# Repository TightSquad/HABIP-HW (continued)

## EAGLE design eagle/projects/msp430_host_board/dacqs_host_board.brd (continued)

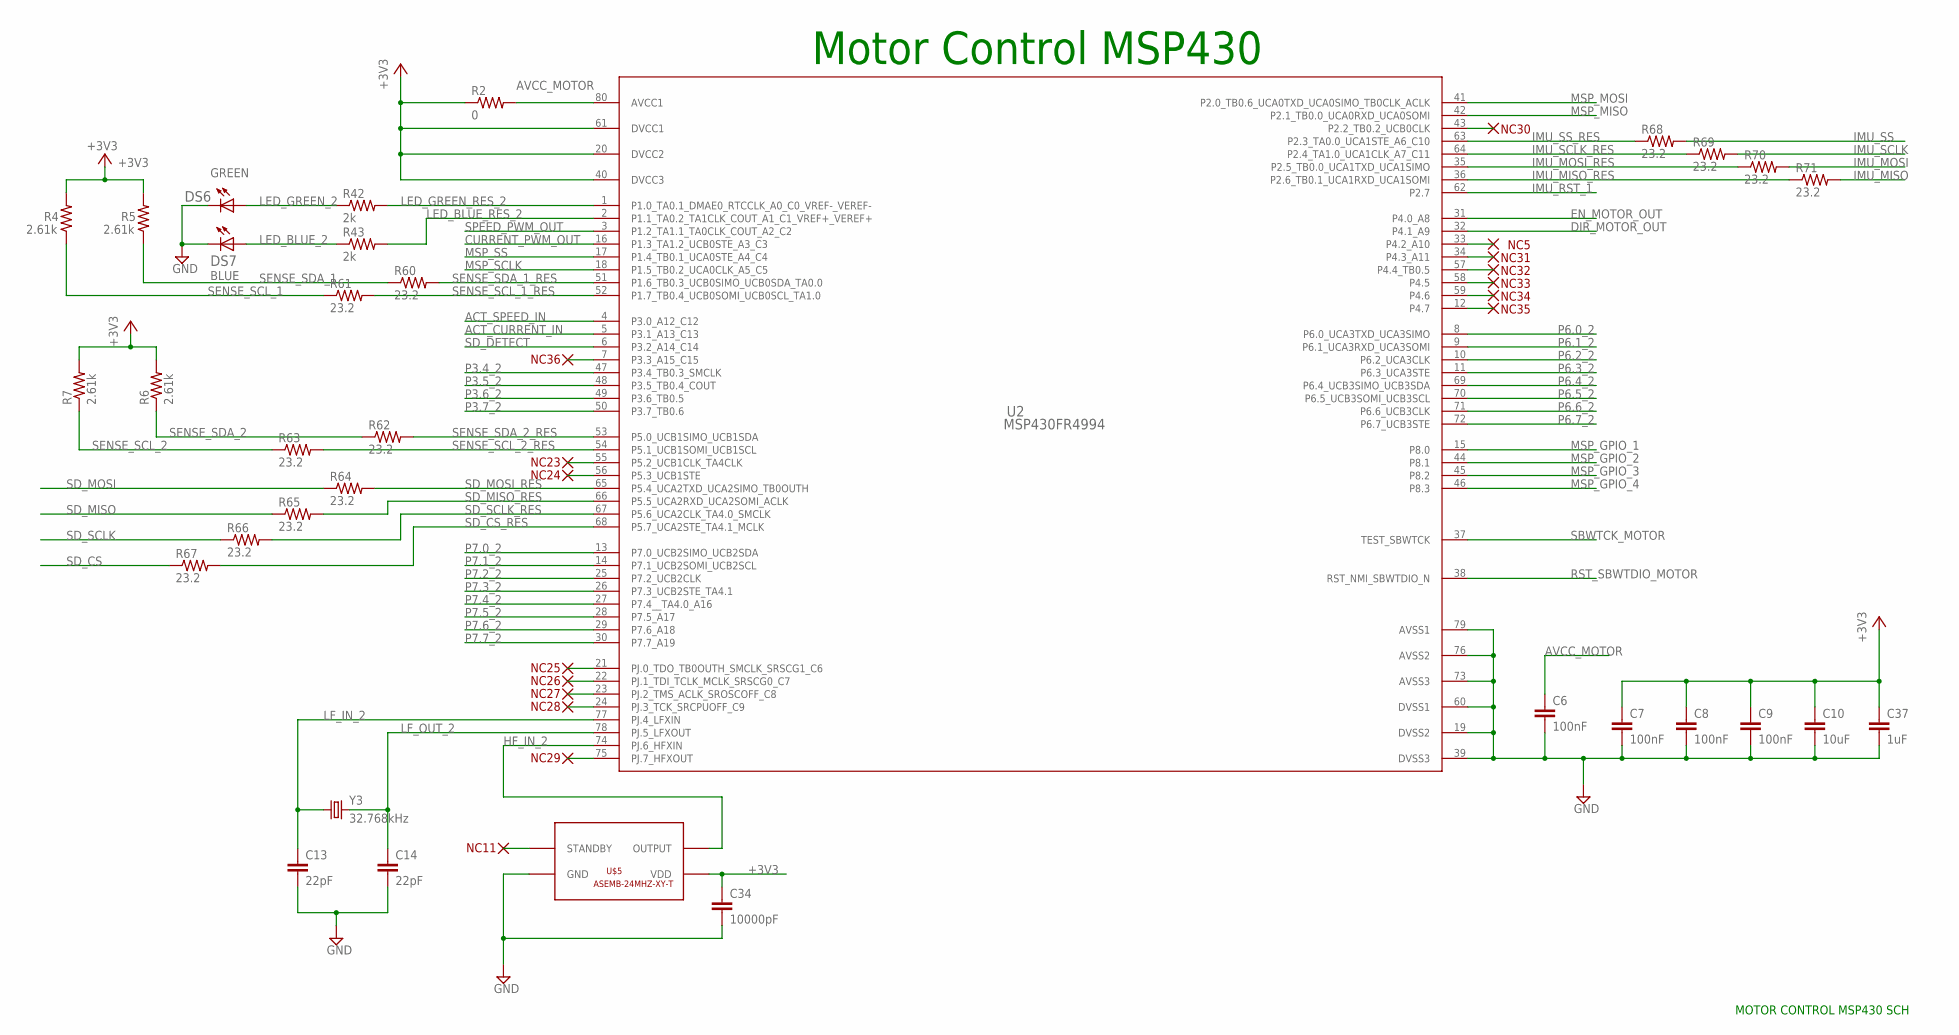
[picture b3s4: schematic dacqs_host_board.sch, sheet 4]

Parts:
C6, C7, C8, C9: 100nF; C0603
C10: 10uF; C0603
C13, C14: 22pF; C0603
C34: 10000pF; C0603
C37: 1uF; C0603
DS6: GREEN; LED0603
DS7: BLUE; LED0603
R2: 0; R0603
R4, R5, R6, R7: 2.61k; R0603
R42, R43: 2k; R0603
R60, R61, R62, R63, R64, R65, R66, R67, R68, R69, R70, R71: 23.2; R0603
U2: MSP430FR4994; PN0080A_N
U$5: ASEMB-24MHZ-XY-T; ASEMB-24MHZ-XY-T-PAC
Y3: 32.768kHz; CRYSTAL-SMD-3.2X1.5MM

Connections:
+3V3: C7.1, C8.1, C9.1, C10.1, C34.1, C37.1, R2.1, R4.2, R5.2, R6.2, R7.2, U2.20 (DVCC2), U2.40 (DVCC3), U2.61 (DVCC1), U$5.P$4 (VDD); also elsewhere on the board
ACT_CURRENT_IN: U2.5 (P3.1_A13_C13); also elsewhere on the board
ACT_SPEED_IN: U2.4 (P3.0_A12_C12); also elsewhere on the board
AVCC_MOTOR: C6.1, R2.2, U2.80 (AVCC1)
CURRENT_PWM_OUT: U2.16 (P1.3_TA1.2_UCB0STE_A3_C3); also elsewhere on the board
DIR_MOTOR_OUT: U2.32 (P4.1_A9); also elsewhere on the board
EN_MOTOR_OUT: U2.31 (P4.0_A8); also elsewhere on the board
GND: C6.2, C7.2, C8.2, C9.2, C10.2, C13.2, C14.2, C34.2, C37.2, DS6.1 (C), DS7.1 (C), U2.19 (DVSS2), U2.39 (DVSS3), U2.60 (DVSS1), U2.73 (AVSS3), U2.76 (AVSS2), U2.79 (AVSS1), U$5.P$2 (GND); also elsewhere on the board
HF_IN_2: U2.74 (PJ.6_HFXIN), U$5.P$3 (OUTPUT)
IMU_MISO: R71.2; also elsewhere on the board
IMU_MISO_RES: R71.1, U2.36 (P2.6_TB0.1_UCA1RXD_UCA1SOMI)
IMU_MOSI: R70.2; also elsewhere on the board
IMU_MOSI_RES: R70.1, U2.35 (P2.5_TB0.0_UCA1TXD_UCA1SIMO)
IMU_RST_1: U2.62 (P2.7); also elsewhere on the board
IMU_SCLK: R69.2; also elsewhere on the board
IMU_SCLK_RES: R69.1, U2.64 (P2.4_TA1.0_UCA1CLK_A7_C11)
IMU_SS: R68.2; also elsewhere on the board
IMU_SS_RES: R68.1, U2.63 (P2.3_TA0.0_UCA1STE_A6_C10)
LED_BLUE_2: DS7.2 (A), R43.1
LED_BLUE_RES_2: R43.2, U2.2 (P1.1_TA0.2_TA1CLK_COUT_A1_C1_VREF+_VERE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)
LED_GREEN_2: DS6.2 (A), R42.1
LED_GREEN_RES_2: R42.2, U2.1 (P1.0_TA0.1_DMAE0_RTCCLK_A0_C0_VREF-_VER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)
LF_IN_2: C13.1, U2.77 (PJ.4_LFXIN), Y3.P$1 (1)
LF_OUT_2: C14.1, U2.78 (PJ.5_LFXOUT), Y3.P$2 (2)
MSP_GPIO_1: U2.15 (P8.0); also elsewhere on the board
MSP_GPIO_2: U2.44 (P8.1); also elsewhere on the board
MSP_GPIO_3: U2.45 (P8.2); also elsewhere on the board
MSP_GPIO_4: U2.46 (P8.3); also elsewhere on the board
MSP_MISO: U2.42 (P2.1_TB0.0_UCA0RXD_UCA0SOMI); also elsewhere on the board
MSP_MOSI: U2.41 (P2.0_TB0.6_UCA0TXD_UCA0SIMO_TB0CLK_ACLK); also elsewhere on the board
MSP_SCLK: U2.18 (P1.5_TB0.2_UCA0CLK_A5_C5); also elsewhere on the board
MSP_SS: U2.17 (P1.4_TB0.1_UCA0STE_A4_C4); also elsewhere on the board
P3.4_2: U2.47 (P3.4_TB0.3_SMCLK); also elsewhere on the board
P3.5_2: U2.48 (P3.5_TB0.4_COUT); also elsewhere on the board
P3.6_2: U2.49 (P3.6_TB0.5); also elsewhere on the board
P3.7_2: U2.50 (P3.7_TB0.6); also elsewhere on the board
P6.0_2: U2.8 (P6.0_UCA3TXD_UCA3SIMO); also elsewhere on the board
P6.1_2: U2.9 (P6.1_UCA3RXD_UCA3SOMI); also elsewhere on the board
P6.2_2: U2.10 (P6.2_UCA3CLK); also elsewhere on the board
P6.3_2: U2.11 (P6.3_UCA3STE); also elsewhere on the board
P6.4_2: U2.69 (P6.4_UCB3SIMO_UCB3SDA)
P6.5_2: U2.70 (P6.5_UCB3SOMI_UCB3SCL); also elsewhere on the board
P6.6_2: U2.71 (P6.6_UCB3CLK); also elsewhere on the board
P6.7_2: U2.72 (P6.7_UCB3STE); also elsewhere on the board
P7.0_2: U2.13 (P7.0_UCB2SIMO_UCB2SDA); also elsewhere on the board
P7.1_2: U2.14 (P7.1_UCB2SOMI_UCB2SCL); also elsewhere on the board
P7.2_2: U2.25 (P7.2_UCB2CLK); also elsewhere on the board
P7.3_2: U2.26 (P7.3_UCB2STE_TA4.1); also elsewhere on the board
P7.4_2: U2.27 (P7.4__TA4.0_A16); also elsewhere on the board
P7.5_2: U2.28 (P7.5_A17); also elsewhere on the board
P7.6_2: U2.29 (P7.6_A18); also elsewhere on the board
P7.7_2: U2.30 (P7.7_A19); also elsewhere on the board
RST_SBWTDIO_MOTOR: U2.38 (RST_NMI_SBWTDIO_N); also elsewhere on the board
SBWTCK_MOTOR: U2.37 (TEST_SBWTCK); also elsewhere on the board
SD_CS: R67.1; also elsewhere on the board
SD_CS_RES: R67.2, U2.68 (P5.7_UCA2STE_TA4.1_MCLK)
SD_DETECT: U2.6 (P3.2_A14_C14); also elsewhere on the board
SD_MISO: R65.1; also elsewhere on the board
SD_MISO_RES: R65.2, U2.66 (P5.5_UCA2RXD_UCA2SOMI_ACLK)
SD_MOSI: R64.1; also elsewhere on the board
SD_MOSI_RES: R64.2, U2.65 (P5.4_UCA2TXD_UCA2SIMO_TB0OUTH)
SD_SCLK: R66.1; also elsewhere on the board
SD_SCLK_RES: R66.2, U2.67 (P5.6_UCA2CLK_TA4.0_SMCLK)
SENSE_SCL_1: R4.1, R61.1; also elsewhere on the board
SENSE_SCL_1_RES: R61.2, U2.52 (P1.7_TB0.4_UCB0SOMI_UCB0SCL_TA1.0)
SENSE_SCL_2: R7.1, R63.1; also elsewhere on the board
SENSE_SCL_2_RES: R63.2, U2.54 (P5.1_UCB1SOMI_UCB1SCL)
SENSE_SDA_1: R5.1, R60.1; also elsewhere on the board
SENSE_SDA_1_RES: R60.2, U2.51 (P1.6_TB0.3_UCB0SIMO_UCB0SDA_TA0.0)
SENSE_SDA_2: R6.1, R62.1; also elsewhere on the board
SENSE_SDA_2_RES: R62.2, U2.53 (P5.0_UCB1SIMO_UCB1SDA)
SPEED_PWM_OUT: U2.3 (P1.2_TA1.1_TA0CLK_COUT_A2_C2); also elsewhere on the board

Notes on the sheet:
Motor Control MSP430
MOTOR CONTROL MSP430 SCH

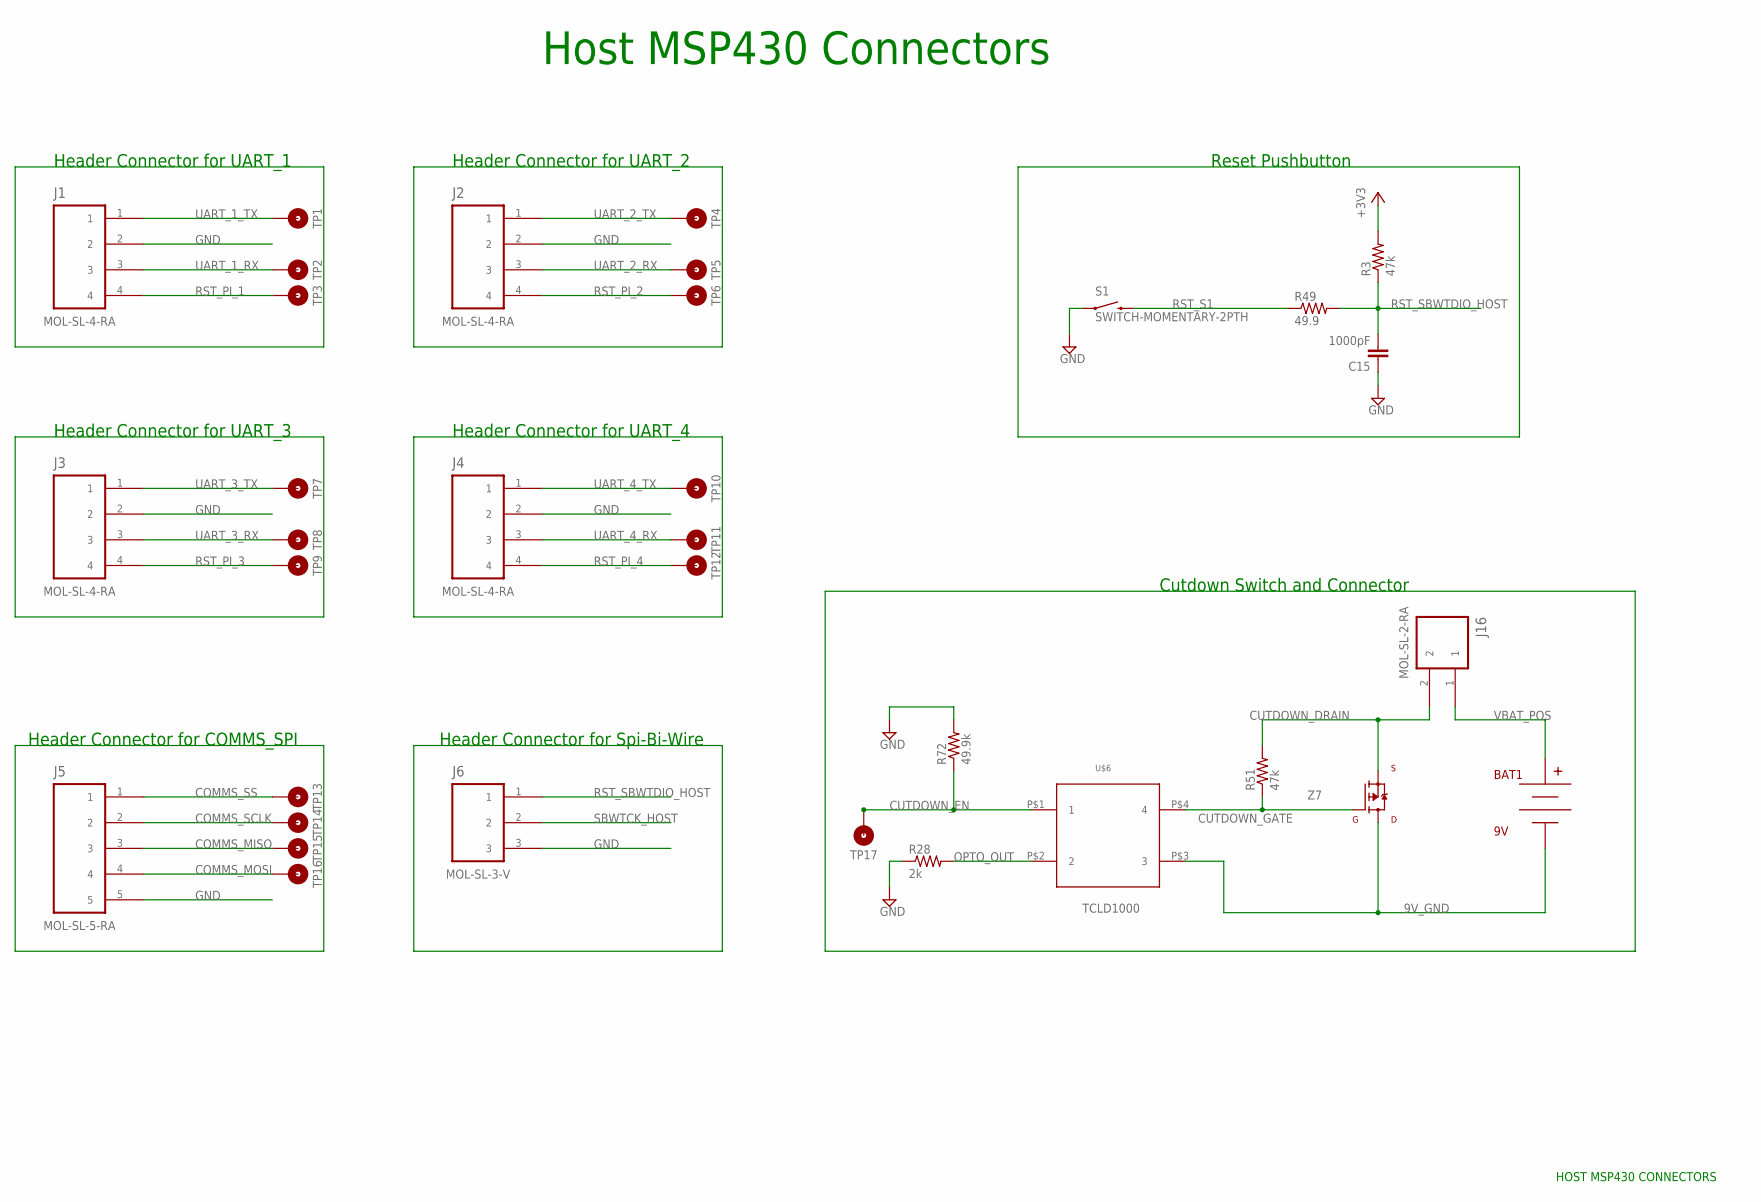
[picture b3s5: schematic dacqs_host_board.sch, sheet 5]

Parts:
BAT1: 9V; BC9VPC
C15: 1000pF; C0603
J1, J2, J3, J4: MOL-SL-4-RA; MOLSL-4-RA
J5: MOL-SL-5-RA; MOLSL-5-RA
J6: MOL-SL-3-V; MOLSL-3-V
J16: MOL-SL-2-RA; MOLSL-2-RA
R3, R51: 47k; R0603
R28: 2k; R0603
R49: 49.9; R0603
R72: 49.9k; R0603
S1: SWITCH-MOMENTARY-2PTH; TACTILE-PTH
TP1, TP2, TP3, TP4, TP5, TP6, TP7, TP8, TP9, TP10, TP11, TP12, TP13, TP14, TP15, TP16, TP17: TEST_POINT_TP10R_SMD_10R_SMD; TP10R
U$6: TCLD1000
Z7: NTD2955T4G

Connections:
9V_GND: BAT1.V-, U$6.P$3 (3), Z7.P$3 (D)
+3V3: R3.2; also elsewhere on the board
COMMS_MISO: J5.3, TP15.TP; also elsewhere on the board
COMMS_MOSI: J5.4, TP16.TP; also elsewhere on the board
COMMS_SCLK: J5.2, TP14.TP; also elsewhere on the board
COMMS_SS: J5.1, TP13.TP; also elsewhere on the board
CUTDOWN_DRAIN: J16.2, R51.2, Z7.P$2 (S)
CUTDOWN_EN: R72.1, TP17.TP, U$6.P$1 (1); also elsewhere on the board
CUTDOWN_GATE: R51.1, U$6.P$4 (4), Z7.P$1 (G)
GND: C15.1, J1.2, J2.2, J3.2, J4.2, J5.5, J6.3, R28.1, R72.2, S1.1; also elsewhere on the board
OPTO_OUT: R28.2, U$6.P$2 (2)
RST_PI_1: J1.4, TP3.TP; also elsewhere on the board
RST_PI_2: J2.4, TP6.TP; also elsewhere on the board
RST_PI_3: J3.4, TP9.TP; also elsewhere on the board
RST_PI_4: J4.4, TP12.TP; also elsewhere on the board
RST_S1: R49.1, S1.3 (2)
RST_SBWTDIO_HOST: C15.2, J6.1, R3.1, R49.2; also elsewhere on the board
SBWTCK_HOST: J6.2; also elsewhere on the board
UART_1_RX: J1.3, TP2.TP; also elsewhere on the board
UART_1_TX: J1.1, TP1.TP; also elsewhere on the board
UART_2_RX: J2.3, TP5.TP; also elsewhere on the board
UART_2_TX: J2.1, TP4.TP; also elsewhere on the board
UART_3_RX: J3.3, TP8.TP; also elsewhere on the board
UART_3_TX: J3.1, TP7.TP; also elsewhere on the board
UART_4_RX: J4.3, TP11.TP; also elsewhere on the board
UART_4_TX: J4.1, TP10.TP; also elsewhere on the board
VBAT_POS: BAT1.V+, J16.1

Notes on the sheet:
Header Connector for UART_1
Header Connector for UART_2
Header Connector for UART_3
Header Connector for UART_4
Header Connector for COMMS_SPI
Reset Pushbutton
Header Connector for Spi-Bi-Wire
Cutdown Switch and Connector
Host MSP430 Connectors
HOST MSP430 CONNECTORS

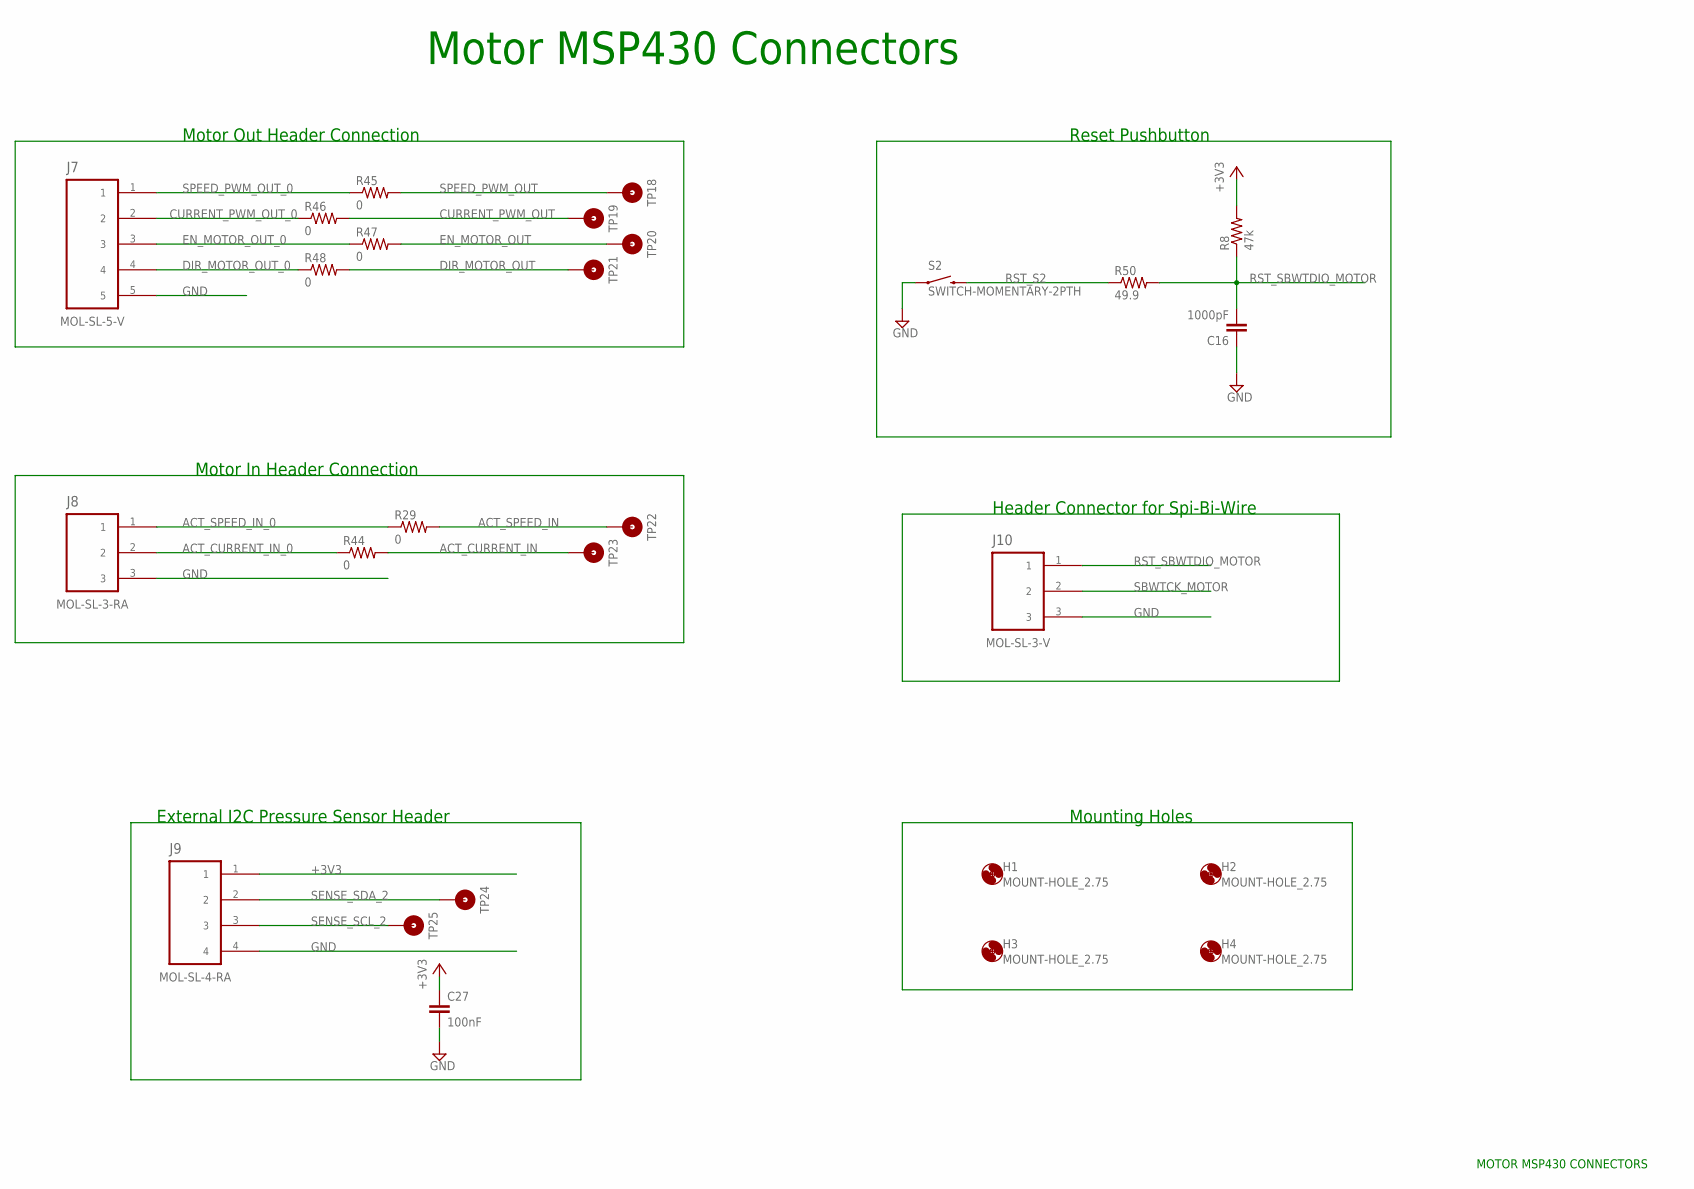
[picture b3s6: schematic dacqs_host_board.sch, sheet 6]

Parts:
C16: 1000pF; C0603
C27: 100nF; C0603
H1, H2, H3, H4: MOUNT-HOLE_2.75; 2,75_HOLE_RASPI
J7: MOL-SL-5-V; MOLSL-5-V
J8: MOL-SL-3-RA; MOLSL-3-RA
J9: MOL-SL-4-RA; MOLSL-4-RA
J10: MOL-SL-3-V; MOLSL-3-V
R8: 47k; R0603
R29, R44, R45, R46, R47, R48: 0; R0603
R50: 49.9; R0603
S2: SWITCH-MOMENTARY-2PTH; TACTILE-PTH
TP18, TP19, TP20, TP21, TP22, TP23, TP24, TP25: TEST_POINT_TP10R_SMD_10R_SMD; TP10R

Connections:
+3V3: C27.1, J9.1, R8.2; also elsewhere on the board
ACT_CURRENT_IN: R44.2, TP23.TP; also elsewhere on the board
ACT_CURRENT_IN_0: J8.2, R44.1
ACT_SPEED_IN: R29.2, TP22.TP; also elsewhere on the board
ACT_SPEED_IN_0: J8.1, R29.1
CURRENT_PWM_OUT: R46.2, TP19.TP; also elsewhere on the board
CURRENT_PWM_OUT_0: J7.2, R46.1
DIR_MOTOR_OUT: R48.2, TP21.TP; also elsewhere on the board
DIR_MOTOR_OUT_0: J7.4, R48.1
EN_MOTOR_OUT: R47.2, TP20.TP; also elsewhere on the board
EN_MOTOR_OUT_0: J7.3, R47.1
GND: C16.1, C27.2, J7.5, J8.3, J9.4, J10.3, S2.1; also elsewhere on the board
RST_S2: R50.1, S2.3 (2)
RST_SBWTDIO_MOTOR: C16.2, J10.1, R8.1, R50.2; also elsewhere on the board
SBWTCK_MOTOR: J10.2; also elsewhere on the board
SENSE_SCL_2: J9.3, TP25.TP; also elsewhere on the board
SENSE_SDA_2: J9.2, TP24.TP; also elsewhere on the board
SPEED_PWM_OUT: R45.2, TP18.TP; also elsewhere on the board
SPEED_PWM_OUT_0: J7.1, R45.1

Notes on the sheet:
Motor Out Header Connection
Motor In Header Connection
External I2C Pressure Sensor Header
Header Connector for Spi-Bi-Wire
Reset Pushbutton
Motor MSP430 Connectors
Mounting Holes
MOTOR MSP430 CONNECTORS

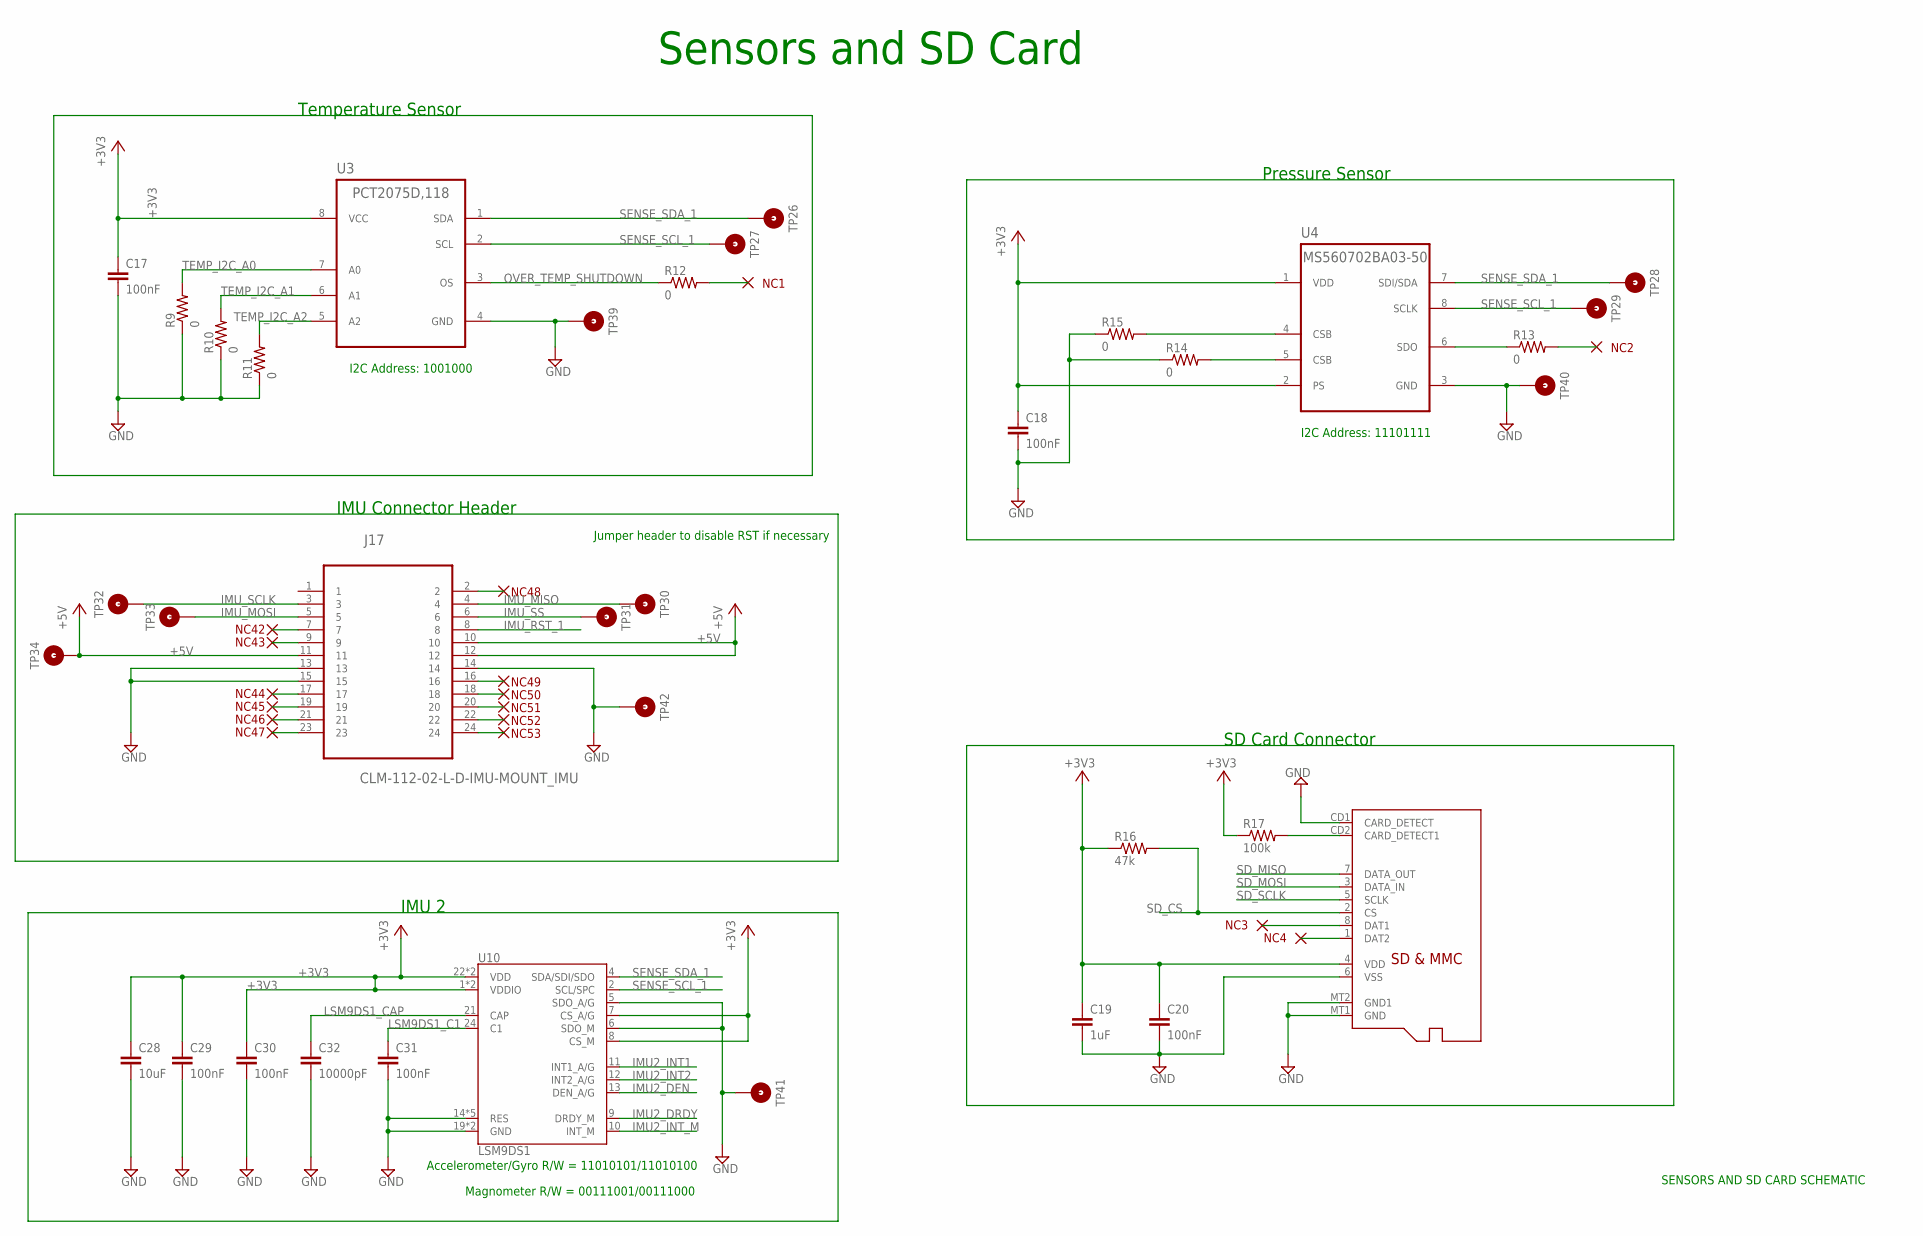
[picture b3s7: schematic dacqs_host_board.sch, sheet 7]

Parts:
C17, C18, C20, C29, C30, C31: 100nF; C0603
C19: 1uF; C0603
C28: 10uF; C0603
C32: 10000pF; C0603
J17: CLM-112-02-L-D-IMU-MOUNT_IMU; SAMTEC_CLM-112-02-L-D-IMU-MOUNT
R9, R10, R11, R12, R13, R14, R15: 0; R0603
R16: 47k; R0603
R17: 100k; R0603
TP26, TP27, TP28, TP29, TP30, TP31, TP32, TP33, TP34, TP39, TP40, TP41, TP42: TEST_POINT_TP10R_SMD_10R_SMD; TP10R
U3: PCT2075D,118; SOIC127P130X0600-8N
U4: MS560702BA03-50; SMD125P110X060-8N
U10: LSM9DS1; LGA24-8X4
U$1: MICROSD

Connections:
+3V3: C17.1, C18.1, C19.1, C20.1, C28.1, C29.1, C30.1, R16.1, R17.1, U3.8 (VCC), U4.1 (VDD), U4.2 (PS), U10.1 (VDDIO), U10.3 (VDDIO), U10.7 (CS_A/G), U10.8 (CS_M), U10.22 (VDD), U10.23 (VDD), U$1.4 (VDD); also elsewhere on the board
+5V: J17.10, J17.11, J17.12, TP34.TP; also elsewhere on the board
GND: C17.2, C18.2, C19.2, C20.2, C28.2, C29.2, C30.2, C31.2, C32.2, J17.13, J17.14, J17.15, R9.1, R10.1, R11.1, R14.1, R15.1, TP39.TP, TP40.TP, TP41.TP, TP42.TP, U3.4 (GND), U4.3 (GND), U10.5 (SDO_A/G), U10.6 (SDO_M), U10.14 (RES), U10.15 (RES), U10.16 (RES), U10.17 (RES), U10.18 (RES), U10.19 (GND), U10.20 (GND), U$1.6 (VSS), U$1.CD1 (CARD_DETECT), U$1.MT1 (GND), U$1.MT2 (GND1); also elsewhere on the board
IMU2_DEN: U10.13 (DEN_A/G); also elsewhere on the board
IMU2_DRDY: U10.9 (DRDY_M); also elsewhere on the board
IMU2_INT1: U10.11 (INT1_A/G); also elsewhere on the board
IMU2_INT2: U10.12 (INT2_A/G); also elsewhere on the board
IMU2_INT_M: U10.10 (INT_M); also elsewhere on the board
IMU_MISO: J17.4, TP30.TP; also elsewhere on the board
IMU_MOSI: J17.5, TP33.TP; also elsewhere on the board
IMU_RST_1: J17.8; also elsewhere on the board
IMU_SCLK: J17.3, TP32.TP; also elsewhere on the board
IMU_SS: J17.6, TP31.TP; also elsewhere on the board
LSM9DS1_C1: C31.1, U10.24 (C1)
LSM9DS1_CAP: C32.1, U10.21 (CAP)
unnamed: R15.2, U4.4 (CSB)
unnamed: R14.2, U4.5 (CSB)
unnamed: R13.1, U4.6 (SDO)
OVER_TEMP_SHUTDOWN: R12.1, U3.3 (OS)
SD_CS: R16.2, U$1.2 (CS); also elsewhere on the board
SD_DETECT: R17.2, U$1.CD2 (CARD_DETECT1); also elsewhere on the board
SD_MISO: U$1.7 (DATA_OUT); also elsewhere on the board
SD_MOSI: U$1.3 (DATA_IN); also elsewhere on the board
SD_SCLK: U$1.5 (SCLK); also elsewhere on the board
SENSE_SCL_1: TP27.TP, TP29.TP, U3.2 (SCL), U4.8 (SCLK), U10.2 (SCL/SPC); also elsewhere on the board
SENSE_SDA_1: TP26.TP, TP28.TP, U3.1 (SDA), U4.7 (SDI/SDA), U10.4 (SDA/SDI/SDO); also elsewhere on the board
TEMP_I2C_A0: R9.2, U3.7 (A0)
TEMP_I2C_A1: R10.2, U3.6 (A1)
TEMP_I2C_A2: R11.2, U3.5 (A2)

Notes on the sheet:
Temperature Sensor
Pressure Sensor
IMU Connector Header
Jumper header to disable RST if necessary
SD Card Connector
Sensors and SD Card
IMU 2
SENSORS AND SD CARD SCHEMATIC
I2C Address: 1001000
I2C Address: 11101111
Accelerometer/Gyro R/W = 11010101/11010100
Magnometer R/W = 00111001/00111000

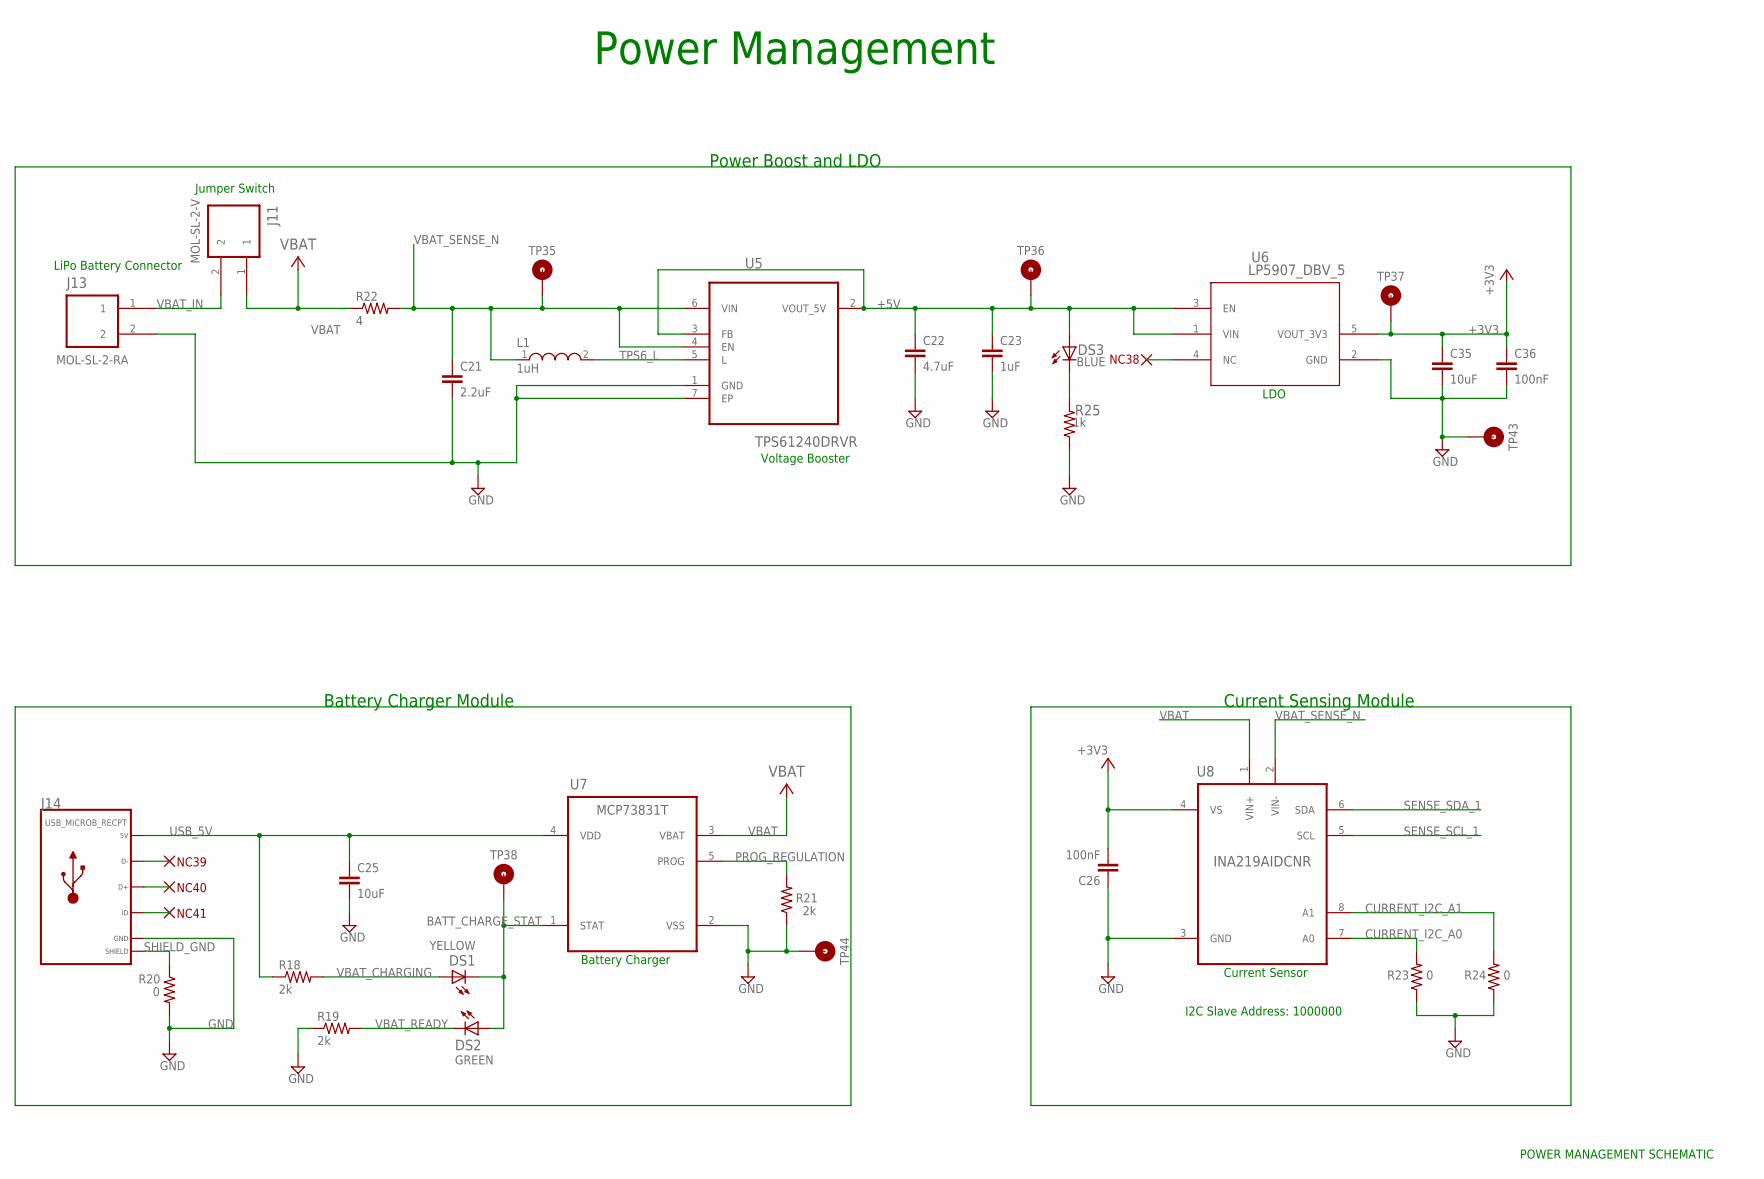
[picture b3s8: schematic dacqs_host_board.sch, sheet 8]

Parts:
C21: 2.2uF; C0603
C22: 4.7uF; C0603
C23: 1uF; C0603
C25, C35: 10uF; C0603
C26, C36: 100nF; C0603
DS1: YELLOW; LED0603
DS2: GREEN; LED0603
DS3: BLUE; LED0603
J11: MOL-SL-2-V; MOLSL-2-V
J13: MOL-SL-2-RA; MOLSL-2-RA
J14: USB_MICROB_RECPT; MICROUSB-RIGHT
L1: 1uH; WE-PMI_0805
R18, R19, R21: 2k; R0603
R20, R23, R24: 0; R0603
R22: 4; R0603
R25: 1k; R0603
TP35, TP36, TP37, TP38, TP43, TP44: TEST_POINT_TP10R_SMD_10R_SMD; TP10R
U5: TPS61240DRVR; SON65P200X200X80-7N
U6: LP5907_DBV_5; DBV5
U7: MCP73831T; SOT23P110X060-5N
U8: INA219AIDCNR; SOT65P110X045-8N

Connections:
+3V3: C26.2, C35.1, C36.1, TP37.TP, U6.5 (VOUT_3V3), U8.4 (VS); also elsewhere on the board
+5V: C22.1, C23.1, DS3.2 (A), TP36.TP, U5.2 (VOUT_5V), U5.3 (FB), U6.1 (VIN), U6.3 (EN); also elsewhere on the board
BATT_CHARGE_STAT: DS1.1 (C), DS2.2 (A), TP38.TP, U7.1 (STAT)
CURRENT_I2C_A0: R23.2, U8.7 (A0)
CURRENT_I2C_A1: R24.2, U8.8 (A1)
GND: C21.2, C22.2, C23.2, C25.2, C26.1, C35.2, C36.2, J13.2, J14.5 (GND), R19.1, R20.2, R21.1, R23.1, R24.1, R25.1, TP43.TP, TP44.TP, U5.1 (GND), U5.7 (EP), U6.2 (GND), U7.2 (VSS), U8.3 (GND); also elsewhere on the board
LED_BLUE_5V: DS3.1 (C), R25.2
PROG_REGULATION: R21.2, U7.5 (PROG)
SENSE_SCL_1: U8.5 (SCL); also elsewhere on the board
SENSE_SDA_1: U8.6 (SDA); also elsewhere on the board
SHIELD_GND: J14.S1 (SLD), J14.S2 (SLD), J14.S3 (SLD), J14.S4 (SLD), J14.S5 (SLD), J14.S6 (SLD), R20.1
TPS6_L: L1.2, U5.5 (L)
USB_5V: C25.1, J14.1 (5V), R18.1, U7.4 (VDD)
VBAT: J11.1, R22.1, U7.3 (VBAT), U8.1 (VIN+)
VBAT_CHARGING: DS1.2 (A), R18.2
VBAT_IN: J11.2, J13.1
VBAT_READY: DS2.1 (C), R19.2
VBAT_SENSE_N: C21.1, L1.1, R22.2, TP35.TP, U5.4 (EN), U5.6 (VIN), U8.2 (VIN-)

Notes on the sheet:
Power Management
LiPo Battery Connector
Jumper Switch
Voltage Booster
LDO
Battery Charger
Current Sensor
Battery Charger Module
Current Sensing Module
Power Boost and LDO
POWER MANAGEMENT SCHEMATIC
I2C Slave Address: 1000000

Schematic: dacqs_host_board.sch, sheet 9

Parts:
J12, J19: CONN HEADER 20POS .100" DBL; 2X10
J18: MOLSL-7-RA
R30, R33: 10.2k; R0603
R31: 10.7k; R0603
R32: 4.12k; R0603
R34, R39: 1.02k; R0603
R35: 68.1k; R0603
R36: 7.5k; R0603
R37: 1.37k; R0603
R38: 1.87k; R0603
R40: 4.32k; R0603
R41: 1.5k; R0603
Z1, Z2, Z3, Z4, Z5, Z6: MMSZ5225BT1G

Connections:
+3V3: J12.2; also elsewhere on the board
GND: J12.20, J18.7, J19.14, R36.2, R37.2, R38.2, R39.2, R40.2, R41.2, Z1.P$2, Z2.P$2, Z3.P$2, Z4.P$2, Z5.P$2, Z6.P$2; also elsewhere on the board
IMU2_DEN: J12.19; also elsewhere on the board
IMU2_DRDY: J12.11; also elsewhere on the board
IMU2_INT1: J12.15; also elsewhere on the board
IMU2_INT2: J12.17; also elsewhere on the board
IMU2_INT_M: J12.13; also elsewhere on the board
P1.2: J12.1; also elsewhere on the board
P1.4: J12.3; also elsewhere on the board
P1.5: J12.5; also elsewhere on the board
P3.4_2: J19.1; also elsewhere on the board
P3.5_2: J19.3; also elsewhere on the board
P3.6_2: J19.5; also elsewhere on the board
P3.7_2: J19.7; also elsewhere on the board
P6.0_2: J19.6; also elsewhere on the board
P6.1_2: J19.8; also elsewhere on the board
P6.2: J12.8; also elsewhere on the board
P6.2_2: J19.10; also elsewhere on the board
P6.3: J12.10; also elsewhere on the board
P6.3_2: J19.12; also elsewhere on the board
P6.4: J12.12; also elsewhere on the board
P6.5: J12.14; also elsewhere on the board
P6.5_2: J19.16; also elsewhere on the board
P6.6: J12.16; also elsewhere on the board
P6.6_2: J19.18; also elsewhere on the board
P6.7: J12.18; also elsewhere on the board
P6.7_2: J19.20; also elsewhere on the board
P7.0: J12.7; also elsewhere on the board
P7.0_2: J19.9; also elsewhere on the board
P7.1: J12.9; also elsewhere on the board
P7.1_2: J19.11; also elsewhere on the board
P7.2: J12.4; also elsewhere on the board
P7.2_2: J19.13; also elsewhere on the board
P7.3: J12.6; also elsewhere on the board
P7.3_2: J19.15; also elsewhere on the board
P7.4_2: J19.17; also elsewhere on the board
P7.5_2: J19.19; also elsewhere on the board
P7.6_2: J19.2; also elsewhere on the board
P7.7_2: J19.4; also elsewhere on the board
VBAT_CELL_1: J18.1, R35.1
VBAT_CELL_2: J18.2, R30.2
VBAT_CELL_3: J18.3, R31.2
VBAT_CELL_4: J18.4, R32.2
VBAT_CELL_5: J18.5, R33.2
VBAT_CELL_6: J18.6, R34.2
VBAT_MOD_CELL_1: R35.2, R36.1, Z1.P$1; also elsewhere on the board
VBAT_MOD_CELL_2: R30.1, R37.1, Z2.P$1; also elsewhere on the board
VBAT_MOD_CELL_3: R31.1, R38.1, Z3.P$1; also elsewhere on the board
VBAT_MOD_CELL_4: R32.1, R39.1, Z4.P$1; also elsewhere on the board
VBAT_MOD_CELL_5: R33.1, R40.1, Z5.P$1; also elsewhere on the board
VBAT_MOD_CELL_6: R34.1, R41.1, Z6.P$1; also elsewhere on the board

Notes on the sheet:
REACTION WHEEL BATTERY VOLTAGE SENSE
RW BATTERY VOLTAGE SENSE
HOST MSP430 HEADER
MOTOR MSP430 HEADER
MAX: 25.2V
MAX: 21V
MAX: 16.8V
MAX: 12.6V
MAX: 8.4V
MAX: 4.2V

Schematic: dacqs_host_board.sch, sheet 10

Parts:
BOM1, BOM2, BOM3, BOM4, BOM44: SL 70066 4PIN HOUSING; BLANK
BOM5, BOM6, BOM7, BOM8, BOM9, BOM10, BOM11, BOM12, BOM13, BOM14, BOM15, BOM16, BOM17, BOM18, BOM19, BOM20, BOM22, BOM23, BOM24, BOM25, BOM26, BOM28, BOM29, BOM30, BOM32, BOM33, BOM35, BOM36, BOM37, BOM38, BOM39, BOM41, BOM42, BOM43, BOM45, BOM46, BOM47, BOM48, BOM50, BOM51, BOM53, BOM54, BOM56, BOM57, BOM58, BOM59, BOM60, BOM61, BOM62: SL 70058 GOLD CRIMP; BLANK
BOM21, BOM34: SL 70066 5PIN HOUSING; BLANK
BOM27, BOM40: SL 70066 3PIN HOUSING; BLANK
BOM31, BOM49, BOM52: SL 70066 2PIN HOUSING; BLANK
BOM55: SL 70066 7PIN HOUSING; BLANK
BOM63: 1-Cell 2500mAh Li-Ion Battery; BLANK

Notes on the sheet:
HOUSING AND CRIMPS
PIHAT UART 1
PIHAT UART 2
PIHAT UART 3
PIHAT UART 4
COMMS SPI CONNECTION
SPY-BY-WIRE CONNECTION
CUTDOWN CONNECTION
MOTOT OUT CONNECTION
MOTOR IN CONNECTION
EXTERNAL PRESSURE CONNECTION
BOARD BATTERY IN CONNECTION
BOARD BATTERY JUMPER SWITCH CONNECTION
MOTOR BATTERY VOLTAGE SENSE
BOARD BATTERY
